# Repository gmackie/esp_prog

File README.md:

# esp_prog
Programmer for the esp8266

This is a board that can be connected via micro USB to program an esp8266 board that uses the 6 pin header documented [here]() This allows quick and easy programming of esp8266 boards for simple IoT projects

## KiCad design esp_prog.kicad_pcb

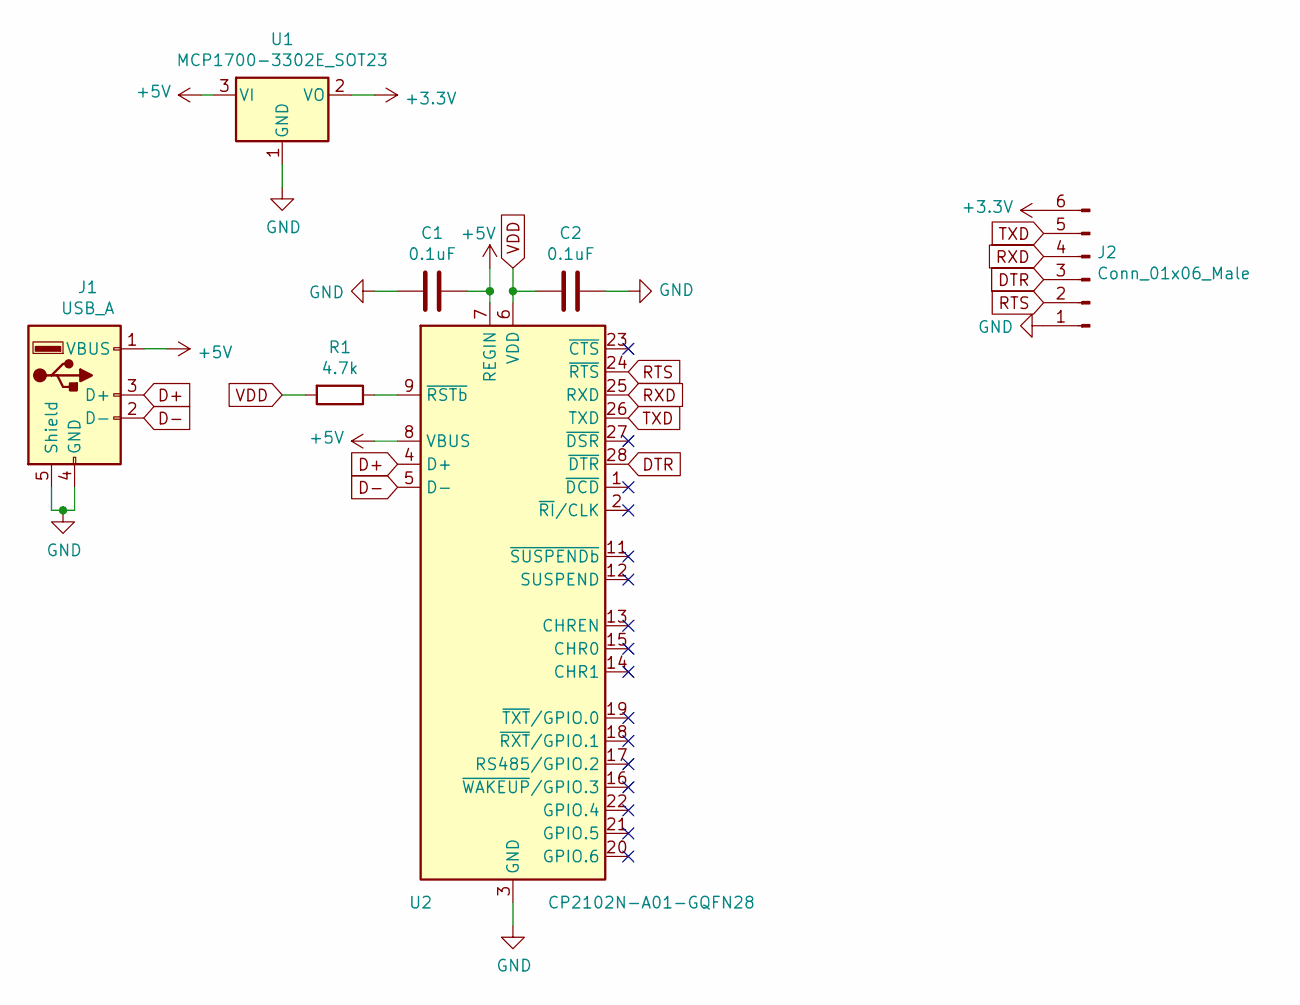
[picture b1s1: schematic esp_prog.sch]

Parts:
C1, C2: 0.1uF; C_0603_1608Metric_Pad1.08x0.95mm_HandSolder
J1: USB_A; USB_A_CNCTech_1001-011-01101_Horizontal
J2: Conn_01x06_Male; JST_XH_B6B-XH-A_1x06_P2.50mm_Vertical
R1: 4.7k; R_0603_1608Metric_Pad0.98x0.95mm_HandSolder
U1: MCP1700-3302E_SOT23; SOT-23
U2: CP2102N-A01-GQFN28; QFN-28-1EP_5x5mm_P0.5mm_EP3.35x3.35mm

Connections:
+3V3: J2.6, U1.2 (VO)
+5V: C1.2, J1.1 (VBUS), U1.3 (VI), U2.7 (REGIN), U2.8 (VBUS)
D+: J1.3 (D+), U2.4 (D+)
D-: J1.2 (D-), U2.5 (D-)
DTR: J2.3, U2.28 (~DTR)
GND: C1.1, C2.2, J1.4 (GND), J1.5 (Shield), J2.1, U1.1 (GND), U2.3 (GND), U2.29 (GND)
unnamed: R1.1, U2.9 (~RSTb)
RTS: J2.2, U2.24 (~RTS)
RXD: J2.4, U2.25 (RXD)
TXD: J2.5, U2.26 (TXD)
VDD: C2.1, R1.2, U2.6 (VDD)

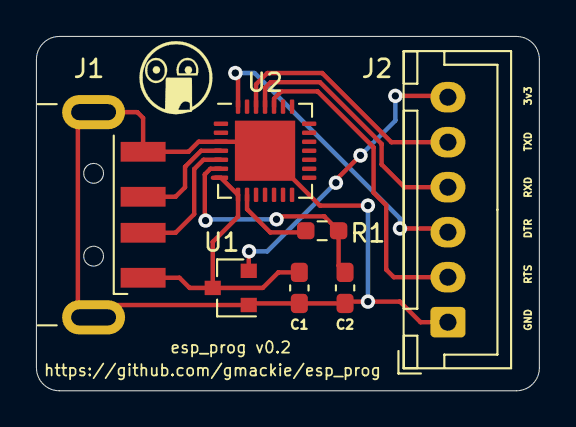
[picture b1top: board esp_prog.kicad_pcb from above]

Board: 2 copper layers, 27.9 x 19.7 mm, 7 parts (0 on the bottom side), 11 nets.

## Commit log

2021-04-24 created board v0.1
2021-04-24 Create LICENSE
2021-05-30 v2, need to add leds and things
